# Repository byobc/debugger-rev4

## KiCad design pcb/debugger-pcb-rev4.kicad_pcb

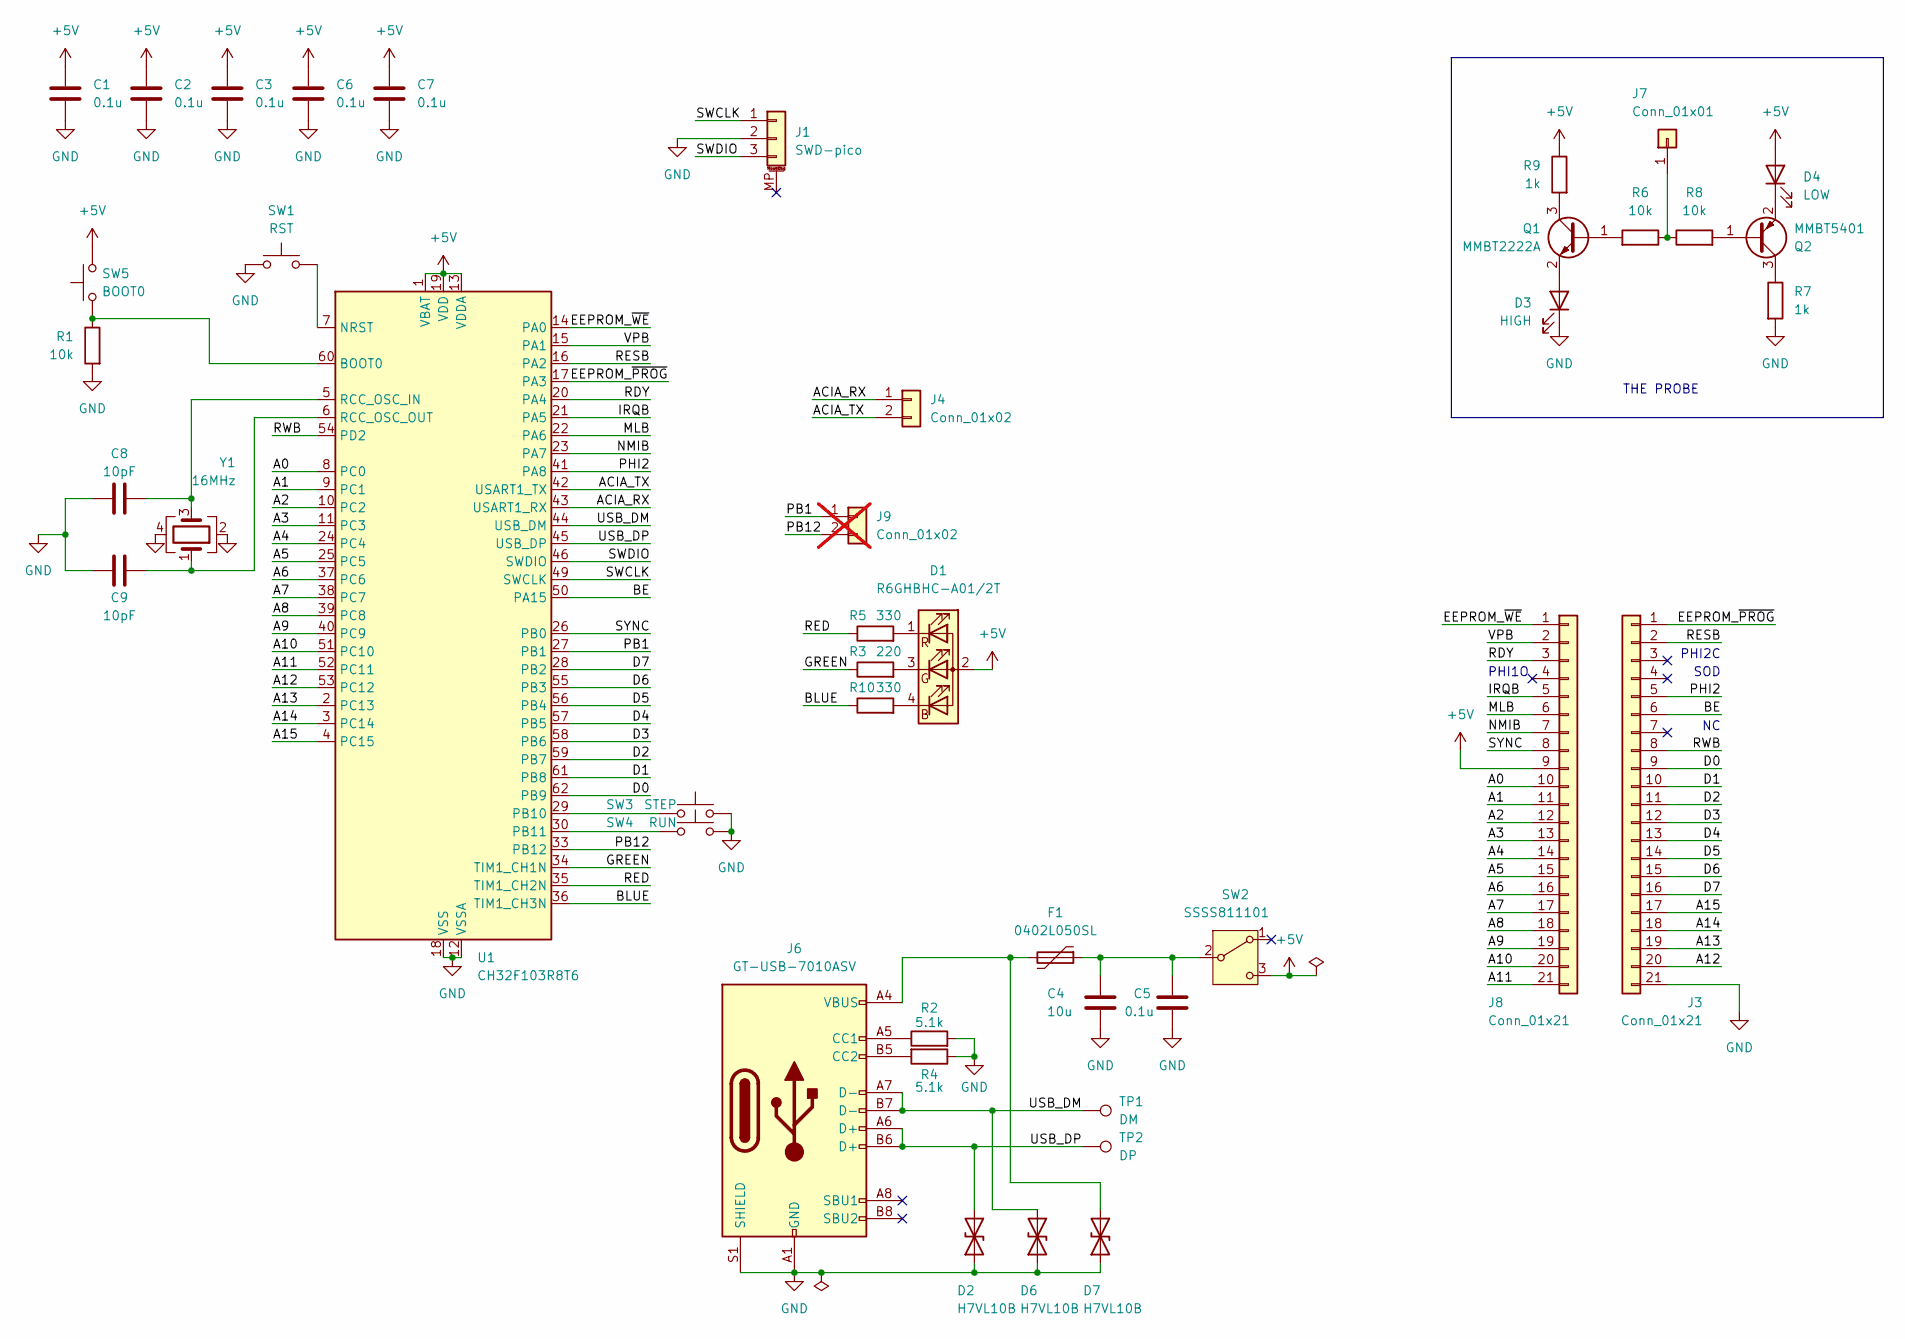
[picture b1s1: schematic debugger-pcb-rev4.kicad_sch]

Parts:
C1, C2, C3, C5, C6, C7: 0.1u; C_0402_1005Metric; JLC P/N C1525
C4: 10u; C_0402_1005Metric; JLC P/N C15525
C8, C9: 10pF; C_0402_1005Metric; JLC P/N C32949
D1: R6GHBHC-A01/2T; Everlight_0606; JLC P/N C60105
D2, D6, D7: H7VL10B; D_SOD-882; JLC P/N C20615787
D3: HIGH; LED_0805_2012Metric; JLC P/N C2297
D4: LOW; LED_0805_2012Metric; JLC P/N C98225
F1: 0402L050SL; Fuse_0402_1005Metric; JLC P/N C206938
J1: SWD-pico; JST_SH_BM03B-SRSS-TB_1x03-1MP_P1.00mm_Vertical; JLC P/N C3029333
J3, J8: Conn_01x21; PinHeader_1x21_P2.54mm_Vertical_nosilk
J4: Conn_01x02; PinHeader_1x02_P2.54mm_Vertical
J6: GT-USB-7010ASV; USB_C_Receptacle_GCT_USB4105-xx-A_16P_TopMnt_Horizontal; JLC P/N C2988369
J7: Conn_01x01; PinHeader_1x01_P2.54mm_Vertical
J9: Conn_01x02; PinHeader_1x02_P2.54mm_Vertical; not fitted
Q1: MMBT2222A; SOT-523; JLC P/N C94417
Q2: MMBT5401; SOT-523; JLC P/N C2836079
R1, R6, R8: 10k; R_0402_1005Metric; JLC P/N C25744
R2, R4: 5.1k; R_0402_1005Metric; JLC P/N C25905
R3: 220; R_0402_1005Metric; JLC P/N C25091
R5, R10: 330; R_0402_1005Metric; JLC P/N C25104
R7, R9: 1k; R_0402_1005Metric; JLC P/N C11702
SW1: RST; SW_Push_SPST_TS-1088; JLC P/N C720477
SW2: SSSS811101; SW_SPDT_PCM12; JLC P/N C109335
SW3: STEP; SW_Push_SPST_TS-1088; JLC P/N C720477
SW4: RUN; SW_Push_SPST_TS-1088; JLC P/N C720477
SW5: BOOT0; SW_Push_SPST_TS-1088; JLC P/N C720477
TP1: DM; TestPoint_Pad_1.0x1.0mm
TP2: DP; TestPoint_Pad_1.0x1.0mm
U1: CH32F103R8T6; LQFP-64_10x10mm_P0.5mm; JLC P/N C2683478
Y1: 16MHz; Crystal_SMD_3225-4Pin_3.2x2.5mm; JLC P/N C13738

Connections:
+5V: C1.1, C2.1, C3.1, C6.1, C7.1, D1.2 (A), D4.2 (A), J8.9, R9.1, SW2.3 (C), SW5.1, U1.1 (VBAT), U1.13 (VDDA), U1.19 (VDD), U1.32 (VDD), U1.48 (VDD), U1.64 (VDD)
/A0: J8.10, U1.8 (PC0)
/A1: J8.11, U1.9 (PC1)
/A2: J8.12, U1.10 (PC2)
/A3: J8.13, U1.11 (PC3)
/A4: J8.14, U1.24 (PC4)
/A5: J8.15, U1.25 (PC5)
/A6: J8.16, U1.37 (PC6)
/A7: J8.17, U1.38 (PC7)
/A8: J8.18, U1.39 (PC8)
/A9: J8.19, U1.40 (PC9)
/A10: J8.20, U1.51 (PC10)
/A11: J8.21, U1.52 (PC11)
/A12: J3.20, U1.53 (PC12)
/A13: J3.19, U1.2 (PC13)
/A14: J3.18, U1.3 (PC14)
/A15: J3.17, U1.4 (PC15)
/ACIA_RX: J4.1, U1.43 (USART1_RX)
/ACIA_TX: J4.2, U1.42 (USART1_TX)
/BE: J3.6, U1.50 (PA15)
/BLUE: R10.1, U1.36 (TIM1_CH3N)
/D0: J3.9, U1.62 (PB9)
/D1: J3.10, U1.61 (PB8)
/D2: J3.11, U1.59 (PB7)
/D3: J3.12, U1.58 (PB6)
/D4: J3.13, U1.57 (PB5)
/D5: J3.14, U1.56 (PB4)
/D6: J3.15, U1.55 (PB3)
/D7: J3.16, U1.28 (PB2)
/EEPROM_~PROG: J3.1, U1.17 (PA3)
/EEPROM_~WE: J8.1, U1.14 (PA0)
/GREEN: R3.1, U1.34 (TIM1_CH1N)
/IRQB: J8.5, U1.21 (PA5)
/MLB: J8.6, U1.22 (PA6)
/NMIB: J8.7, U1.23 (PA7)
/PB1: J9.1, U1.27 (PB1)
/PB12: J9.2, U1.33 (PB12)
/PHI2: J3.5, U1.41 (PA8)
/RDY: J8.3, U1.20 (PA4)
/RED: R5.1, U1.35 (TIM1_CH2N)
/RESB: J3.2, U1.16 (PA2)
/RWB: J3.8, U1.54 (PD2)
/SWCLK: J1.1, U1.49 (SWCLK)
/SWDIO: J1.3, U1.46 (SWDIO)
/SYNC: J8.8, U1.26 (PB0)
/USB_DM: D6.2 (A2), J6.A7 (D-), J6.B7 (D-), TP1.1, U1.44 (USB_DM)
/USB_DP: D2.2 (A2), J6.A6 (D+), J6.B6 (D+), TP2.1, U1.45 (USB_DP)
/VPB: J8.2, U1.15 (PA1)
GND: C1.2, C2.2, C3.2, C4.2, C5.2, C6.2, C7.2, C8.1, C9.1, D2.1 (A1), D3.1 (K), D6.1 (A1), D7.1 (A1), J1.2, J3.21, J6.A1 (GND), J6.A12 (GND), J6.B1 (GND), J6.B12 (GND), J6.S1 (SHIELD), R1.2, R2.2, R4.1, R7.2, SW1.1, SW3.1, SW4.1, U1.12 (VSSA), U1.18 (VSS), U1.31 (VSS), U1.47 (VSS), U1.63 (VSS), Y1.2, Y1.4
unnamed: D1.4 (BK), R10.2
unnamed: D1.3 (GK), R3.2
unnamed: D1.1 (RK), R5.2
unnamed: D3.2 (A), Q1.2 (E)
unnamed: D4.1 (K), Q2.2 (E)
unnamed: D7.2 (A2), F1.2, J6.A4 (VBUS), J6.A9 (VBUS), J6.B4 (VBUS), J6.B9 (VBUS)
unnamed: J6.A5 (CC1), R2.1
unnamed: J6.B5 (CC2), R4.2
unnamed: J7.1, R6.1, R8.1
unnamed: Q1.1 (B), R6.2
unnamed: Q1.3 (C), R9.2
unnamed: Q2.1 (B), R8.2
unnamed: Q2.3 (C), R7.1
unnamed: C4.1, C5.1, F1.1, SW2.2 (B)
unnamed: R1.1, SW5.2, U1.60 (BOOT0)
unnamed: SW1.2, U1.7 (NRST)
unnamed: SW3.2, U1.29 (PB10)
unnamed: SW4.2, U1.30 (PB11)
unnamed: C8.2, U1.5 (RCC_OSC_IN), Y1.3
unnamed: C9.2, U1.6 (RCC_OSC_OUT), Y1.1

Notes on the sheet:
SOD
THE PROBE
PHI2C
PHI1O

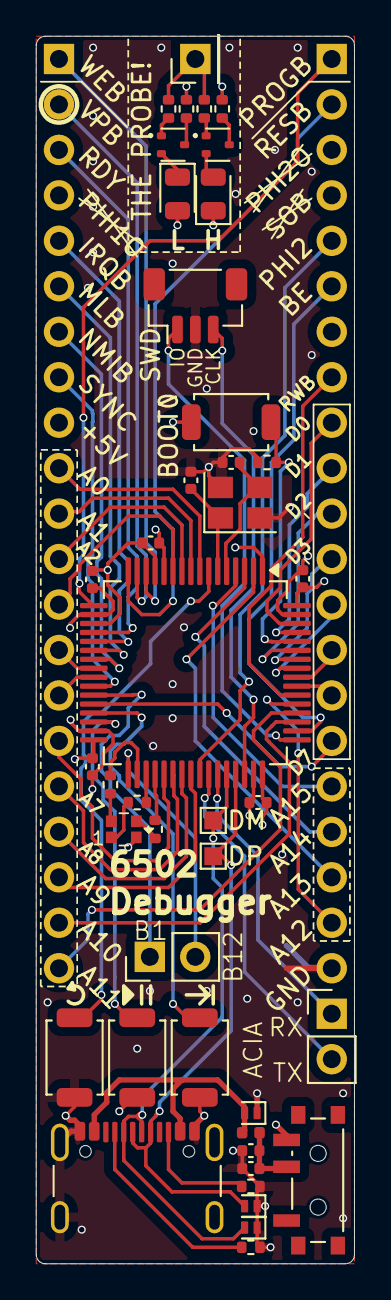
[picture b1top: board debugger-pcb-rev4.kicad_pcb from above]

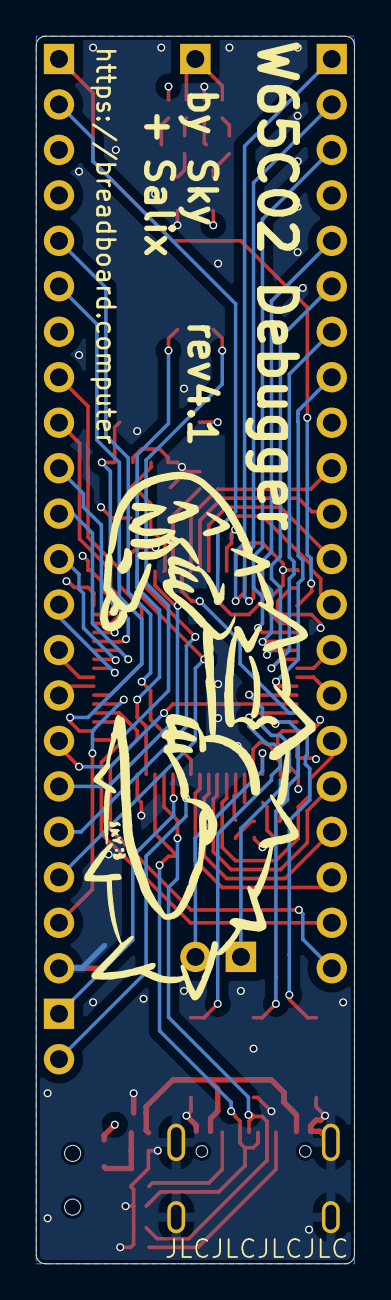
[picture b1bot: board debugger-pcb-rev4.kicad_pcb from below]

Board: 4 copper layers, 17.8 x 68.6 mm, 44 parts (2 on the bottom side), 69 nets.

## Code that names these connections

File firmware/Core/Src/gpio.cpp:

#include "gpio.h"
#include "stm32f103xb.h"
#include "stm32f1xx_hal.h" // IWYU pragma: keep
#include "stm32f1xx_hal_gpio.h"
#include "stm32f1xx_hal_tim.h"
// #include "pins.h"

#define DATA_PINS_MASK 0b1111111100 // PB2:9
#define ADDR_PINS_MASK 0xffff // PC0:15

extern TIM_HandleTypeDef htim1;

#define IO_DEF(_state, _port, _pin) \
	void set_ ## _state ## _dir(Direction dir, bool pullup) { \
		GPIO_InitTypeDef init { \
			.Pin = _pin, \
			.Mode = (dir == Direction::Input) ? GPIO_MODE_INPUT : GPIO_MODE_OUTPUT_PP, \
			.Pull = (pullup) ? GPIO_PULLUP : GPIO_NOPULL, \
			.Speed = GPIO_SPEED_FREQ_LOW, \
		}; \
		HAL_GPIO_Init(_port, &init); \
	} \
	bool read_ ## _state() { \
		return HAL_GPIO_ReadPin(_port, _pin); \
	} \
	void write_ ## _state(bool level) { \
		HAL_GPIO_WritePin(_port, _pin, static_cast<GPIO_PinState>(level)); \
	}


namespace gpio {
	void set_addr_bus_mode(AddressBusMode mode) {
		switch (mode) {
			case AddressBusMode::CpuDriven:
				set_addr_bus_dir(Direction::Input);
				write_be(true);
				break;
			case AddressBusMode::DebuggerDriven:
				write_be(false);
				set_addr_bus_dir(Direction::Output);
				break;
		}
	}

	static uint8_t reverse_u8(uint8_t x) {
		// TODO: rbit?
		x = ((x & 0xf0) >> 4) | ((x & 0x0f) << 4);
		x = ((x & 0xcc) >> 2) | ((x & 0x33) << 2);
		x = ((x & 0xaa) >> 1) | ((x & 0x55) << 1);
		return x;
	}

	void set_data_bus_dir(Direction dir) {
		GPIO_InitTypeDef init {
			.Pin = DATA_PINS_MASK,
			.Mode = (dir == Direction::Input) ? GPIO_MODE_INPUT : GPIO_MODE_OUTPUT_PP,
			.Pull = GPIO_NOPULL,
			.Speed = GPIO_SPEED_FREQ_LOW,
		};
		HAL_GPIO_Init(GPIOB, &init);
	}

	void write_data_bus(uint8_t data) {
		uint32_t out = GPIOB->ODR;
		out &= ~DATA_PINS_MASK;
		out |= reverse_u8(data) << 2;
		GPIOB->ODR = out;
	}

	uint8_t read_data_bus() {
		return reverse_u8(static_cast<uint8_t>(GPIOB->IDR >> 2));
	}

	void set_addr_bus_dir(Direction dir) {
		GPIO_InitTypeDef init {
			.Pin = ADDR_PINS_MASK,
			.Mode = (dir == Direction::Input) ? GPIO_MODE_INPUT : GPIO_MODE_OUTPUT_PP,
			.Pull = GPIO_NOPULL,
			.Speed = GPIO_SPEED_FREQ_LOW,
		};
		HAL_GPIO_Init(GPIOC, &init);
	}

	void write_addr_bus(uint16_t data) {
		GPIOC->ODR = static_cast<uint32_t>(data);
	}

	uint16_t read_addr_bus() {
		return static_cast<uint16_t>(GPIOC->IDR);
	}

	status_t read_status() {
		return {
			static_cast<uint16_t>(
				(read_mlb() << 15) |
				(read_irqb() << 14) |
				(read_rdy() << 11) |
				(read_vpb() << 10) |
				(read_progb() << 9) |
				(read_we() << 8) |
				(read_rwb() << 5) |
				(read_be() << 4) |
				(read_phi2() << 3) |
				(read_resb() << 2) |
				(read_sync() << 1) |
				read_nmib()
			)
		};
	}

	IO_DEF(mlb,   GPIOA, GPIO_PIN_6)
	IO_DEF(irqb,  GPIOA, GPIO_PIN_5)
	IO_DEF(progb, GPIOA, GPIO_PIN_3)
	IO_DEF(phi2,  GPIOA, GPIO_PIN_8)
	IO_DEF(rwb,   GPIOD, GPIO_PIN_2)
	IO_DEF(sync,  GPIOB, GPIO_PIN_0)
	IO_DEF(vpb,   GPIOA, GPIO_PIN_1)
	IO_DEF(resb,  GPIOA, GPIO_PIN_2)
	IO_DEF(nmib,  GPIOA, GPIO_PIN_7)
	IO_DEF(be,    GPIOA, GPIO_PIN_15)
	IO_DEF(we,    GPIOA, GPIO_PIN_0)
	IO_DEF(rdy,   GPIOA, GPIO_PIN_4)

	void setup_rgb() {
		GPIO_InitTypeDef init {
			.Pin = 0xe000,
			.Mode = GPIO_MODE_OUTPUT_PP,
			.Pull = GPIO_NOPULL,
			.Speed = GPIO_SPEED_FREQ_LOW,
		};
		HAL_GPIO_Init(GPIOB, &init);
		HAL_GPIO_WritePin(GPIOB, 0xe000, GPIO_PIN_RESET);

		// HAL_TIM_Base_Init(&htim1);
		// TIM1->
	}

	void write_rgb(uint8_t r, uint8_t g, uint8_t b) {
		
	}
}

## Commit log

2025-05-20 Initial commit: incomplete schematic+routing
2025-05-21 more progress: final overall layout
2025-05-23 close to final
2025-05-31 design reviewed and part #s added
2025-05-31 jlc bom script, fix components
2025-07-13 as ordered for batch 1
2025-09-02 move pcb into subdir
2025-09-02 firmware ported
2025-09-05 initial LED setup
2026-01-02 4.1 board revisions done?
2026-01-22 its not working
2026-01-29 start the big rewrite:tm:
2026-02-05 arrghhh it worksssss
